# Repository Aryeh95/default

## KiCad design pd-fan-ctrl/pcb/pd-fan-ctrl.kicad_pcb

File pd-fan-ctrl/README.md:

# ESPHome fan controller for a Corsi-Rosenthal box

A small board that runs 12 V PWM PC fans from a USB-C PD charger and puts them in Home Assistant
through ESPHome on a Seeed XIAO ESP32-C6. It is sized for a Corsi-Rosenthal air purifier (140 mm
fans such as the Arctic P14 PWM PST), but works for any 4-pin PWM fans.

- Requests 15 V from any USB-C PD charger of 30 W or more and makes a regulated 12 V fan rail.
- Switches the fan rail fully off, so "off" in Home Assistant stops fans that idle at 0 % PWM.
- 25 kHz PWM, RPM from both fan headers, input voltage, charger protocol and available current.
- I2C and UART headers for an air-quality sensor (3.3 V logic).
- Wi-Fi, Thread or Zigbee firmware builds, a KiCad 9 project, JLCPCB order files and a
  3D-printable case.

The board is rev B: the XIAO plugs into two surface-mount sockets and everything else is
surface-mount, so JLCPCB can assemble it with Economic PCBA. It is 52 × 46 mm, 2-layer. Rev A (a
through-hole version with a 5 V module) was cancelled before it was built; it is in the git
history.

## Layout

```
pcb/         KiCad project, fab/ (Gerbers, BOM, CPL) and docs/ (schematic PDF, renders)
esphome/     firmware: one file per network, plus common/ shared by all three
case/        OpenSCAD case model and STL files
scripts/     generators for the board, schematic and order files
```

**Status: designed and rule-checked, not built.** Measure the 5 V and 12 V rails on the first board
before connecting fans or plugging in the XIAO (see [the first-board checks](#things-to-check-on-the-first-board)). The board passes KiCad DRC with 0 violations and
0 unconnected items, and the schematic, PCB and `design.py` netlists match (33 nets / 142 pins).

A version with an ESP32-C6-MINI-1 module soldered to the board was also designed and then set
aside, because JLCPCB only fits that module with Standard PCBA. Its design and generated files are
in the git history.

## Changes from rev A

- **5 V rail:** a second TPS54302 buck (100 k / 13 k feedback, 5.18 V) replaces the K7805
  through-hole module. Its EN pin is left open, so it is always on.
- **12 V inductor:** TMPA0605S-150MN-D (LCSC C305194; 15 µH, 4 A rated and saturation, 73 mΩ,
  7.3 × 6.6 mm) on JLCPCB's land pattern for it. It is in stock at JLCPCB, so no pre-order is needed.
  The inductor would allow about 7 fans, but the TPS54302 then dissipates
  roughly 0.6–0.7 W in a SOT-23-6, so **treat 5 fans as the limit** until a built board has been
  checked for temperature at full load.
- **5 V inductor:** FXL0518-100-M (10 µH, 2.5 A continuous, 3 A saturation) instead of a 1.95 A part,
  so a short on the 5 V header no longer saturates it before the converter's current limit trips.
- **CH224A on the I2C bus:** its CFG2/SCL and CFG3/SDA pins join the XIAO's I2C bus (the datasheet
  allows 3.3 V logic on them; the board's 4.7 k pull-ups serve both). The CH224A still requests
  15 V by itself through its 56 k resistor. The firmware reads which protocol was negotiated and how
  much current the charger offers ("Charger Max Current" / "Charger Max Power"), so you can see
  whether a charger is big enough for your fans. The CH224A uses I2C address 0x22 or 0x23 (the
  datasheet gives both); don't put a sensor at those addresses on the header.
- **PWM driver base resistor R7** is 1 k (was 2.2 k), so Q3 stays saturated with 7 or more fans
  pulling the PWM line up at once.
- **Extra thermal vias** next to the 12 V converter's ground pin, spreading its heat into the
  bottom copper.
- **FAN2 tach** is read on its own pin (GPIO20) with its own 10 k pull-up and 10 k series resistor.
  FAN1's series resistor is also 10 k now, which protects the GPIO from fans that pull tach up to 12 V.
- **USB-C socket:** 16-pin TYPE-C-31-M-12 (its data pins are unused).
- **PD_PG pull-up** removed; the firmware uses the ESP32's internal pull-up.
- **Fan-header peg holes** are 1.3 mm (Molex recommends 1.25 mm; the KiCad library has 1.1 mm) so
  machine-inserted headers seat flat.
- **VBUS test pad (TP1)** next to the 12 V converter, for measuring the charger voltage.
- **Wider supply tracks:** the charger input (VBUS) is 0.8 mm wide (was 0.5 mm) for 7-fan loads, and
  no longer passes through a resistor pad on the way to the 5 V converter. The 12 V fan rail is 1 mm.
- **CH224A ground pad** has two vias straight down to the bottom ground plane (its exposed pad is
  its only ground pin).
- **CH224A DP/DM** are shorted together at the chip and not connected to the USB-C socket, as the
  datasheet describes for PD-only use. This turns off the QC/BC 1.2 fallbacks, which could only
  offer 5–12 V anyway; the fans need the 15 V PD profile.
- **Ground plane:** signal tracks on the bottom layer cut from about 260 mm to 150 mm. Estimated ground
  resistance from the USB-C socket and the 12 V output capacitors to the 12 V converter is now
  0.5–0.7 mΩ (a solid plane would be about 0.4 mΩ).

### Things to check on the first board

- **CH224A VBUS pin (R16):** the datasheet's reference circuit ties it straight to VBUS (as here,
  through R16 = 0 Ω), while its pin table says the pin tolerates 3.8 V. If PD negotiation misbehaves
  or U1 runs hot, this is the first thing to look at.
- **12 V converter temperature** with all fans at 100 %.
- **CH224A I2C:** check the boot log's I2C scan finds it at 0x22 or 0x23, and that "Charger Max
  Current" matches the charger's label. If the CH224A misbehaves with the bus connected, the
  sensors can be removed from the firmware, since it requests 15 V from its resistor with no I2C
  traffic needed.
- **Wi-Fi signal** with the XIAO in its sockets, compared with a bare XIAO (the 5 V converter is
  about 6 mm from the antenna end, 7.5 mm below it).
- Pull the XIAO **straight up** out of the SMD sockets; they're held only by their solder pads.

## Ordering

1. Upload `pcb/fab/*-gerbers.zip`. 2 layers, 1.6 mm, any solder-mask colour (green and blue were
   both quoted with Economic PCBA; colours other than green add about 2 days to the build time),
   HASL with or without lead. Don't pick OSP: that finish forces
   Standard PCBA.
2. PCB Assembly, **Economic**, top side. Upload a BOM and the CPL with the same suffix:
   - `*-jlcpcb.csv`: surface-mount parts only; you solder the fan headers.
   - `*-fanhdr-C19795120.csv`: JLCPCB also fits the fan headers (Molex 470533000). This was quoted
     as Economic PCBA with a small handling fee per header.
3. In the placement preview, check the orientation of U1, U4, U5, Q3, D1, J1, J6, J7 and the fan
   headers (locking ramp along the bottom board edge). L1 and L2 haven't been seen in JLCPCB's
   viewer yet; both are two-pad parts, so only their position matters.

### Seeed Fusion PCBA

The same board can be assembled by Seeed Fusion instead. Seeed buys parts by manufacturer part
number, so it has its own files in `pcb/fab/`:

- `*-gerbers.zip`, the same Gerbers as for JLCPCB.
- `*-bom-seeed.csv` and `*-cpl-seeed.csv`: surface-mount parts only; you solder the fan headers.
- `*-bom-seeed-fanhdr.csv` and `*-cpl-seeed-fanhdr.csv`: Seeed also fits the fan headers
  (Molex 47053-1000, through-hole).
- `*-assembly-top.pdf`: outlines, reference designators and pin-1 marks, for Seeed's
  orientation check.

The BOM has Designator, Manufacturer Part Number, Quantity and an LCSC link for each part, as in
Seeed's template. The placement file uses KiCad's own rotations (the JLCPCB files carry JLCPCB's
corrections). Several parts come from Chinese makers that Seeed may not stock (CH224A, the SMD
sockets, both inductors); the links help their buyers, and Seeed may propose equivalents.

## XIAO notes

- Pin use is the same as rev A, plus D9 (GPIO20) for FAN2 tach.
- Buy bare XIAOs and solder short (about 7.5 mm) 1×7 male headers to them, with the XIAO plugged
  into the board so the pins line up. The SMD sockets have closed bottoms, so long standard headers
  may not seat.
- The sockets are 5 mm tall; the case model assumes that.

## Firmware

There are three builds of the same firmware. Pick one and flash it over the XIAO's own USB
port the first time.

| File | Network | Home Assistant sees | Updates |
|---|---|---|---|
| `pd-fan-ctrl-wifi.yaml` | Wi-Fi, with a fallback hotspot | Fan entity with speed, all sensors | Over Wi-Fi |
| `pd-fan-ctrl-thread.yaml` | Thread (needs a border router) | Same as Wi-Fi | Over Thread |
| `pd-fan-ctrl-zigbee.yaml` | Zigbee router (ZHA or Zigbee2MQTT) | "Fan Power" switch and "Fan Speed" number, the sensors, no "Charger Protocol" | USB only |

- ESPHome can't run Wi-Fi and Thread at the same time, or Zigbee and Thread, so each build
  has one network. To change network, flash a different build: Wi-Fi to Thread works over the
  air; going to Zigbee, or back from Zigbee, needs the USB cable.
- **Thread** needs your network's dataset in `secrets.yaml` as `thread_tlv` (Home Assistant:
  Settings > Devices & services > Thread > Configure > the (i) on your network > Active dataset
  TLVs).
- **Zigbee** support in ESPHome is new and only exposes switches, numbers, sensors and binary
  sensors, so the fan is a switch plus a 0–100 % number and "Reset Filter Hours" is a switch
  that turns itself off. Zigbee2MQTT may show the device as generic endpoints.
- All three were compiled with ESPHome 2026.10.2 but none has run on hardware yet.

### Other XIAO boards

The board takes any XIAO ESP32 with the standard 14-pin layout. Pick yours in the `board:`
line near the top of the firmware file; the board files in `esphome/boards/` hold each chip's
settings and pin numbers.

| Board file | XIAO | Networks | Antenna |
|---|---|---|---|
| `xiao-esp32c6.yaml` (default) | ESP32-C6 | Wi-Fi, Thread, Zigbee | On the board |
| `xiao-esp32c5.yaml` | ESP32-C5 | Wi-Fi (2.4 and 5 GHz), Thread, Zigbee | External, U.FL |
| `xiao-esp32c3.yaml` | ESP32-C3 | Wi-Fi | External, U.FL |
| `xiao-esp32s3.yaml` | ESP32-S3 | Wi-Fi | External, U.FL |
| `xiao-esp32s3-plus.yaml` | ESP32-S3 Plus | Wi-Fi | External, U.FL |

- Boards with an external antenna come with a flexible one; stick it inside the case lid.
- ESPHome warns about "strapping pins" when compiling for the C3, C5 and S3. The board holds
  those pins at safe levels at power-on (see the notes in each board file), so the warnings are
  expected. On the C3, D0 is also pulled low by the voltage divider when no charger is
  connected; this only matters for the boot-button flashing mode, so check USB flashing on the
  first C3.
- The board was designed around the C6. The other boards' pins were checked against Seeed's pin
  maps and their firmware compiles, but none has been tried on the board.

## Files

| Path | What it is |
|---|---|
| `pcb/pd-fan-ctrl.kicad_pro`, `.kicad_sch`, `.kicad_pcb` | KiCad 9 project |
| `pcb/docs/` | Schematic PDF, 3D render, assembly drawing (with reference designators), case preview |
| `pcb/fab/` | Gerbers, JLCPCB BOM and CPL files, hand-solder list |
| `esphome/pd-fan-ctrl-wifi.yaml`, `-thread.yaml`, `-zigbee.yaml` | Firmware, one per network (see [Firmware](#firmware)) |
| `esphome/common/pd-fan-ctrl-core.yaml` | Fan control and sensors shared by all three |
| `esphome/boards/` | Chip settings and pin numbers for each XIAO |
| `case/` | OpenSCAD case model and STL files |
| `scripts/` | Generators |

## Regenerating

```sh
cd scripts
python3 gen_board.py place     # footprints, outline, zones
python3 route.py               # tracks, vias, silkscreen, pour, stitching
python3 drc.py                 # KiCad DRC summary
python3 gen_sch.py             # schematic
python3 check_netlist.py       # schematic == PCB == design.py
python3 gen_fab.py             # Gerbers, BOM, CPL, schematic PDF
```

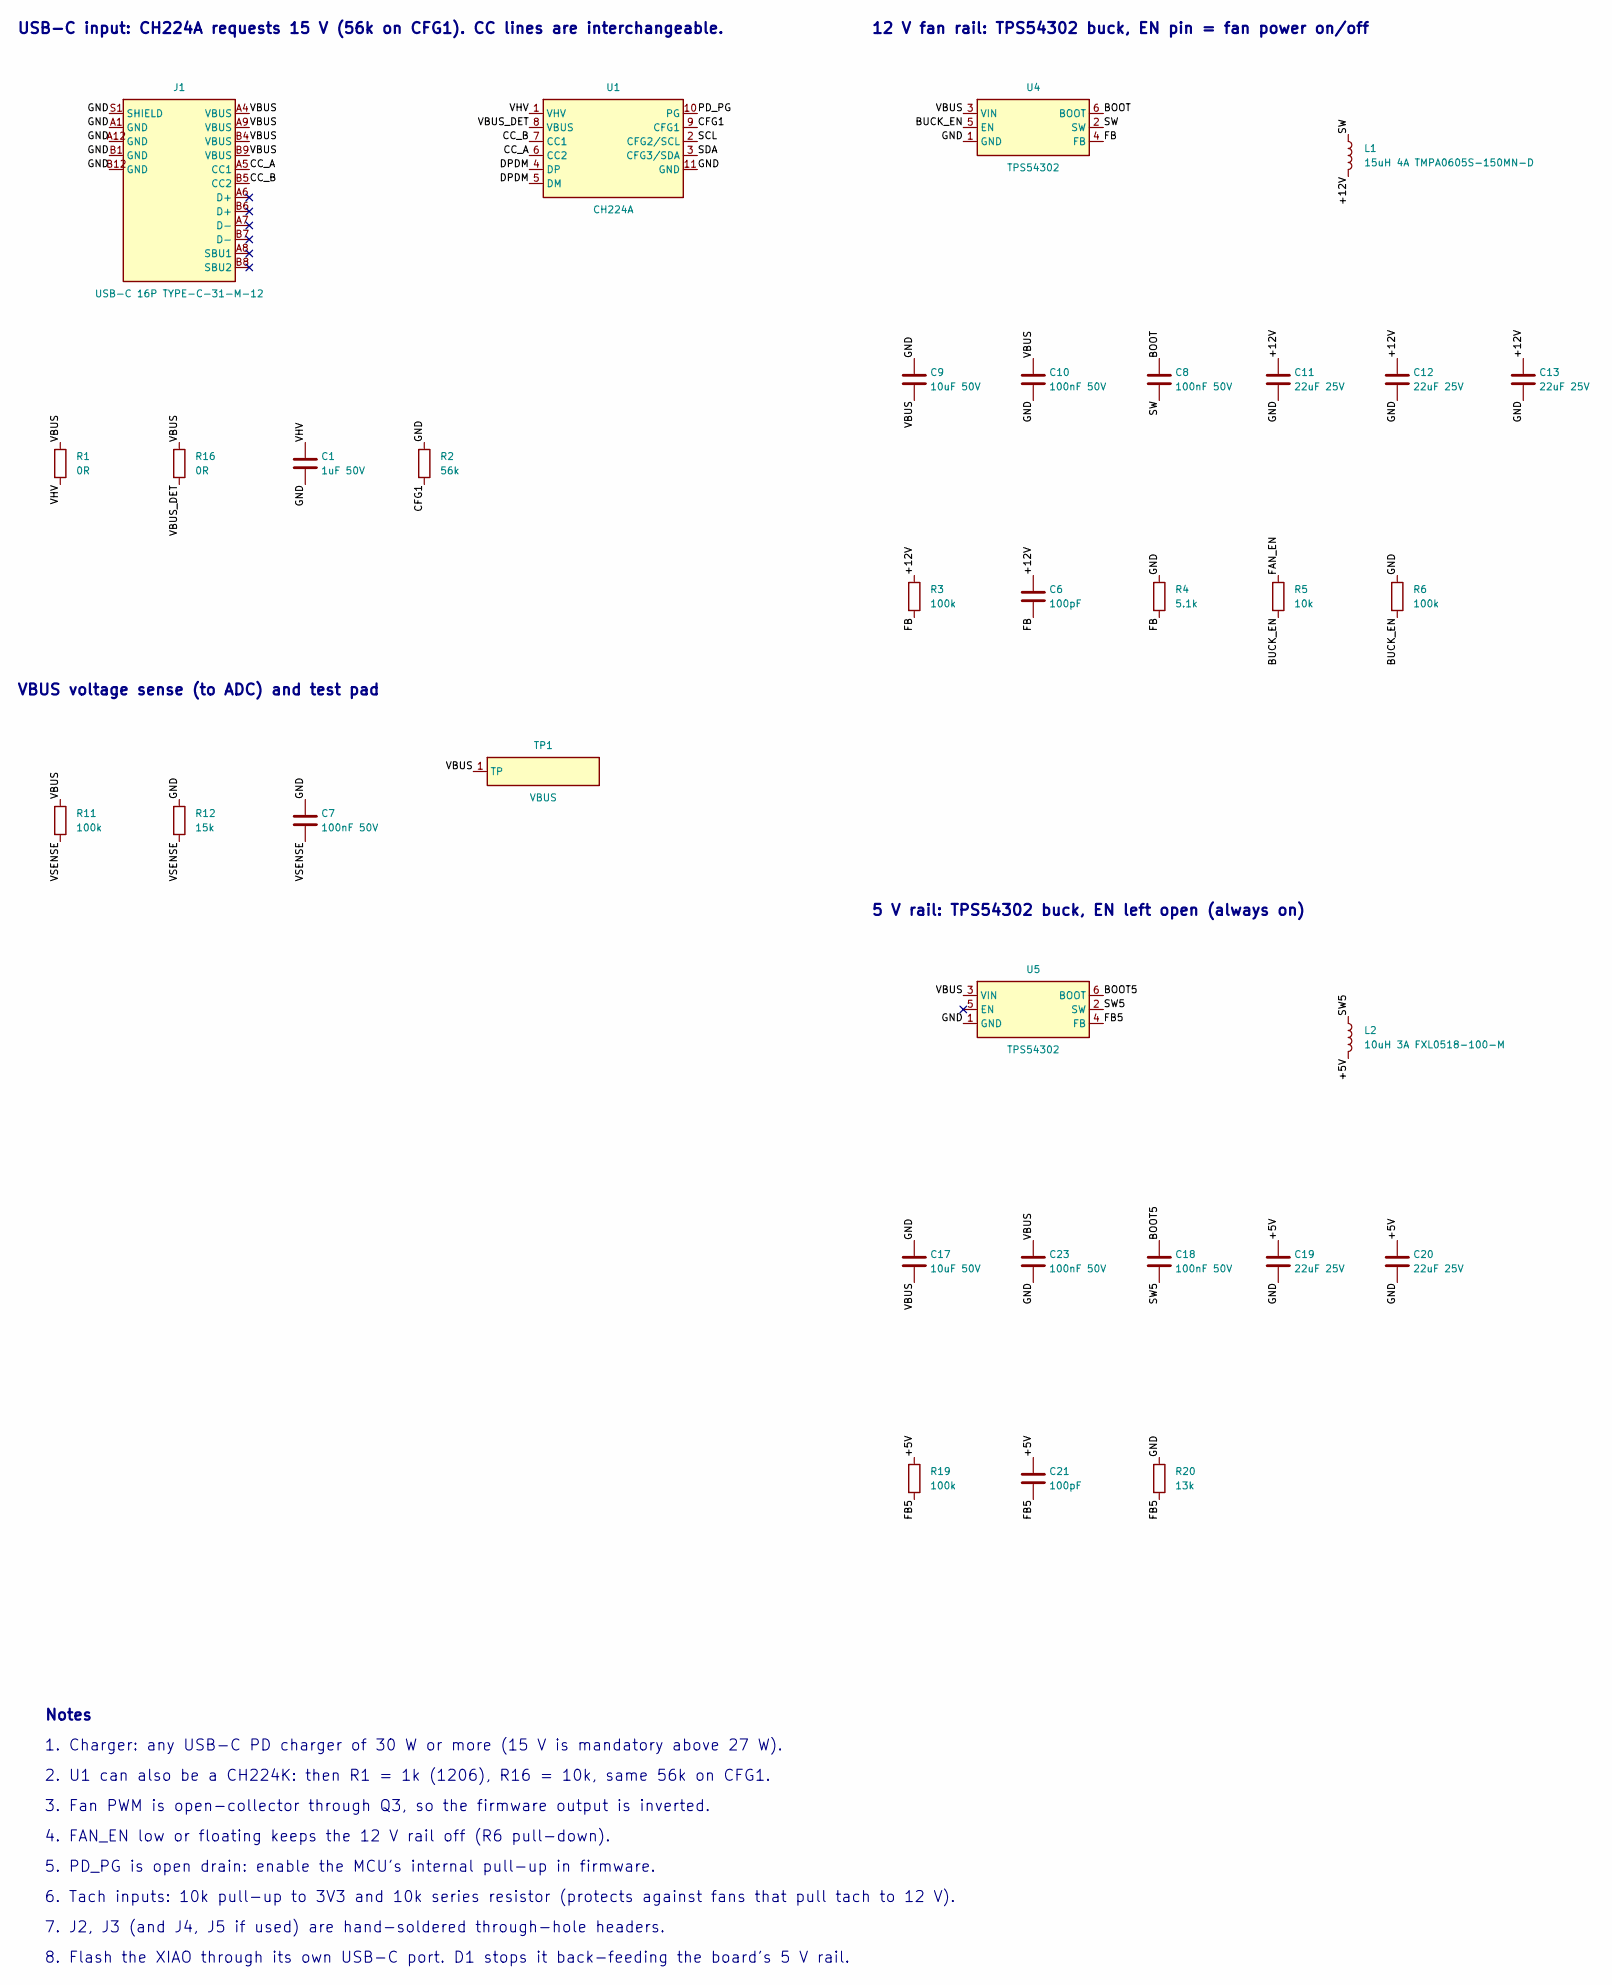
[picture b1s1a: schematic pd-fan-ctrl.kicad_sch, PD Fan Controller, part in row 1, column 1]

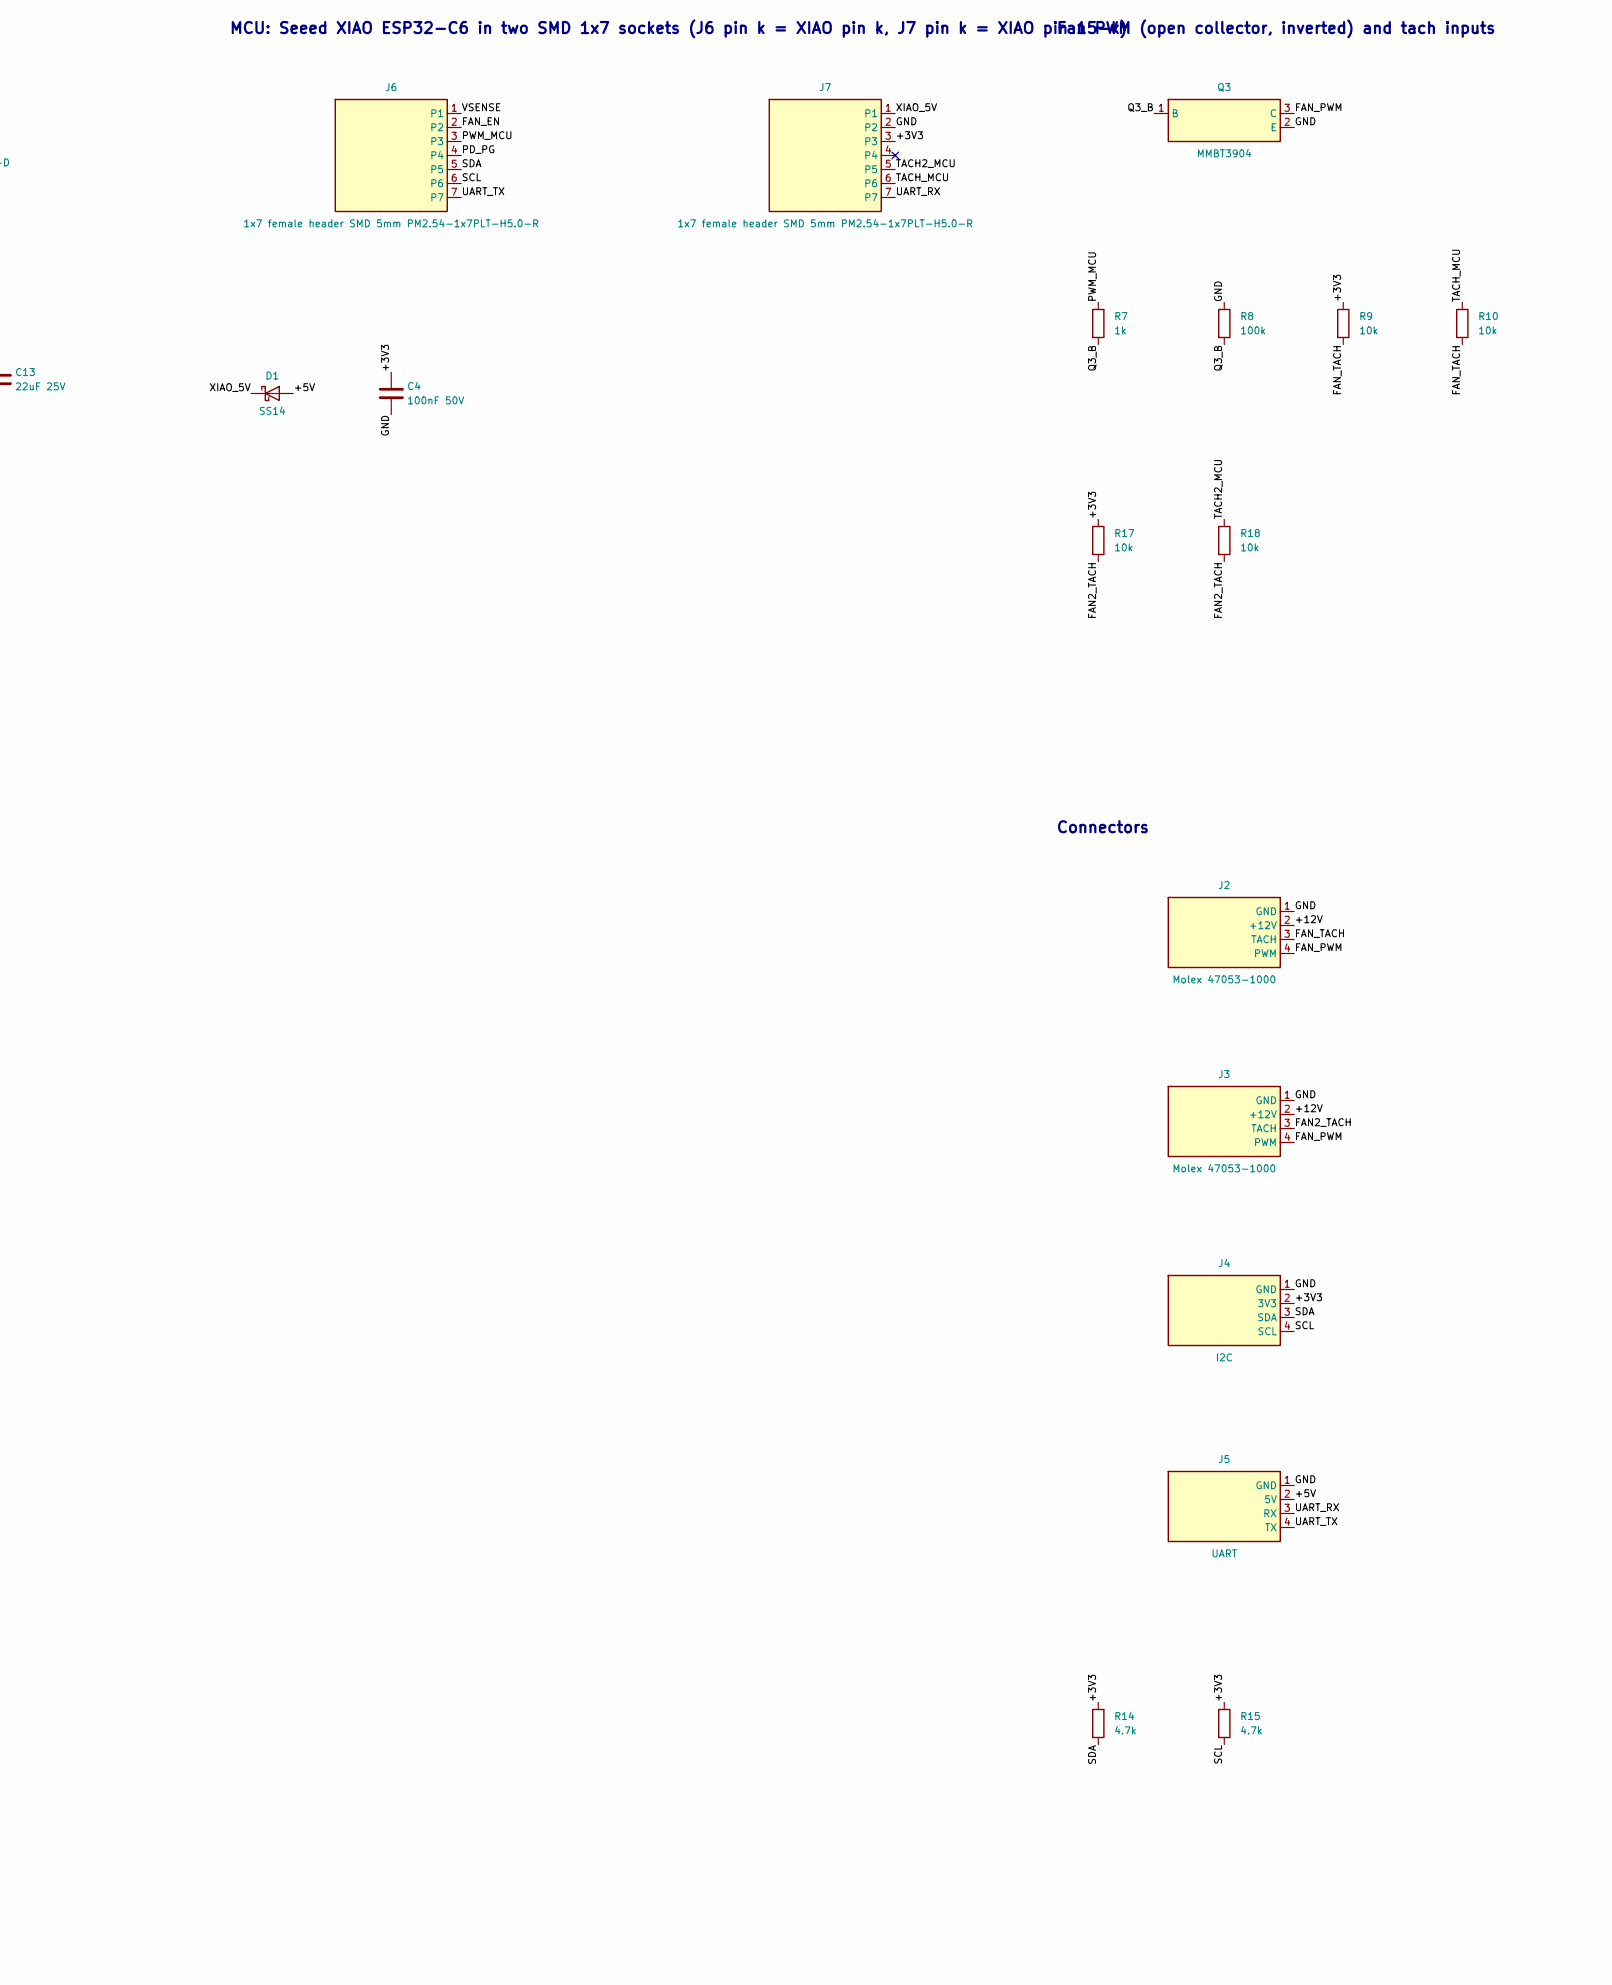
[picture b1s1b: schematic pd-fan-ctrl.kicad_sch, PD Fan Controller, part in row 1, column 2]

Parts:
C1: 1uF 50V; C_0603_1608Metric; LCSC C15849
C4, C7, C8, C10, C18, C23: 100nF 50V; C_0603_1608Metric; LCSC C14663
C6, C21: 100pF; C_0603_1608Metric; LCSC C14858
C9, C17: 10uF 50V; C_1206_3216Metric; LCSC C13585
C11, C12, C13, C19, C20: 22uF 25V; C_1206_3216Metric; LCSC C12891
D1: SS14; D_SMA; LCSC C2480
J1: USB-C 16P TYPE-C-31-M-12; USB_C_Receptacle_HRO_TYPE-C-31-M-12; LCSC C165948
J2, J3: Molex 47053-1000; FanPinHeader_1x04_P2.54mm_Vertical; LCSC C240840
J4: I2C; PinHeader_1x04_P2.54mm_Vertical
J5: UART; PinHeader_1x04_P2.54mm_Vertical
J6, J7: 1x7 female header SMD 5mm PM2.54-1x7PLT-H5.0-R; SOCKET_1x7_SMD; LCSC C55218891
L1: 15uH 4A TMPA0605S-150MN-D; L_TMPA0605S; LCSC C305194
L2: 10uH 3A FXL0518-100-M; L_Changjiang_FXL0518; LCSC C475910
Q3: MMBT3904; SOT-23; LCSC C20526
R1: 0R; R_1206_3216Metric; LCSC C17888
R2: 56k; R_0603_1608Metric; LCSC C23206
R3, R6, R8, R11, R19: 100k; R_0603_1608Metric; LCSC C25803
R4: 5.1k; R_0603_1608Metric; LCSC C23186
R5, R9, R10, R17, R18: 10k; R_0603_1608Metric; LCSC C25804
R7: 1k; R_0603_1608Metric; LCSC C21190
R12: 15k; R_0603_1608Metric; LCSC C22809
R14, R15: 4.7k; R_0603_1608Metric; LCSC C23162
R16: 0R; R_0603_1608Metric; LCSC C21189
R20: 13k; R_0603_1608Metric; LCSC C22797
TP1: VBUS; TestPoint_Pad_D1.5mm
U1: CH224A; SSOP-10-1EP_3.9x4.9mm_P1mm_EP2.1x3.3mm; LCSC C42459160
U4, U5: TPS54302; TSOT-23-6; LCSC C311983

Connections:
+3V3: C4.1, J4.2 (3V3), J7.3, R9.1, R14.1, R15.1, R17.1
+5V: C19.1, C20.1, C21.1, D1.2 (A), J5.2 (5V), L2.2, R19.1
+12V: C6.1, C11.1, C12.1, C13.1, J2.2 (+12V), J3.2 (+12V), L1.2, R3.1
BOOT: C8.1, U4.6 (BOOT)
BOOT5: C18.1, U5.6 (BOOT)
BUCK_EN: R5.2, R6.2, U4.5 (EN)
CC_A: J1.A5 (CC1), U1.6 (CC2)
CC_B: J1.B5 (CC2), U1.7 (CC1)
CFG1: R2.2, U1.9 (CFG1)
DPDM: U1.4 (DP), U1.5 (DM)
FAN2_TACH: J3.3 (TACH), R17.2, R18.2
FAN_EN: J6.2, R5.1
FAN_PWM: J2.4 (PWM), J3.4 (PWM), Q3.3 (C)
FAN_TACH: J2.3 (TACH), R9.2, R10.2
FB: C6.2, R3.2, R4.2, U4.4 (FB)
FB5: C21.2, R19.2, R20.2, U5.4 (FB)
GND: C1.2, C4.2, C7.1, C9.1, C10.2, C11.2, C12.2, C13.2, C17.1, C19.2, C20.2, C23.2, J1.A1 (GND), J1.A12 (GND), J1.B1 (GND), J1.B12 (GND), J1.S1 (SHIELD), J2.1 (GND), J3.1 (GND), J4.1 (GND), J5.1 (GND), J7.2, Q3.2 (E), R2.1, R4.1, R6.1, R8.1, R12.1, R20.1, U1.11 (GND), U4.1 (GND), U5.1 (GND)
PD_PG: J6.4, U1.10 (PG)
PWM_MCU: J6.3, R7.1
Q3_B: Q3.1 (B), R7.2, R8.2
SCL: J4.4 (SCL), J6.6, R15.2, U1.2 (CFG2/SCL)
SDA: J4.3 (SDA), J6.5, R14.2, U1.3 (CFG3/SDA)
SW: C8.2, L1.1, U4.2 (SW)
SW5: C18.2, L2.1, U5.2 (SW)
TACH2_MCU: J7.5, R18.1
TACH_MCU: J7.6, R10.1
UART_RX: J5.3 (RX), J7.7
UART_TX: J5.4 (TX), J6.7
VBUS: C9.2, C10.1, C17.2, C23.1, J1.A4 (VBUS), J1.A9 (VBUS), J1.B4 (VBUS), J1.B9 (VBUS), R1.1, R11.1, R16.1, TP1.1, U4.3 (VIN), U5.3 (VIN)
VBUS_DET: R16.2, U1.8 (VBUS)
VHV: C1.1, R1.2, U1.1 (VHV)
VSENSE: C7.2, J6.1, R11.2, R12.2
XIAO_5V: D1.1 (K), J7.1

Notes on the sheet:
USB-C input: CH224A requests 15 V (56k on CFG1). CC lines are interchangeable.
VBUS voltage sense (to ADC) and test pad
12 V fan rail: TPS54302 buck, EN pin = fan power on/off
5 V rail: TPS54302 buck, EN left open (always on)
Fan PWM (open collector, inverted) and tach inputs
Connectors
MCU: Seeed XIAO ESP32-C6 in two SMD 1x7 sockets (J6 pin k = XIAO pin k, J7 pin k = XIAO pin 15-k)
Notes
1. Charger: any USB-C PD charger of 30 W or more (15 V is mandatory above 27 W).
2. U1 can also be a CH224K: then R1 = 1k (1206), R16 = 10k, same 56k on CFG1.
3. Fan PWM is open-collector through Q3, so the firmware output is inverted.
4. FAN_EN low or floating keeps the 12 V rail off (R6 pull-down).
5. PD_PG is open drain: enable the MCU's internal pull-up in firmware.
6. Tach inputs: 10k pull-up to 3V3 and 10k series resistor (protects against fans that pull tach to 12 V).
7. J2, J3 (and J4, J5 if used) are hand-soldered through-hole headers.
8. Flash the XIAO through its own USB-C port. D1 stops it back-feeding the board's 5 V rail.

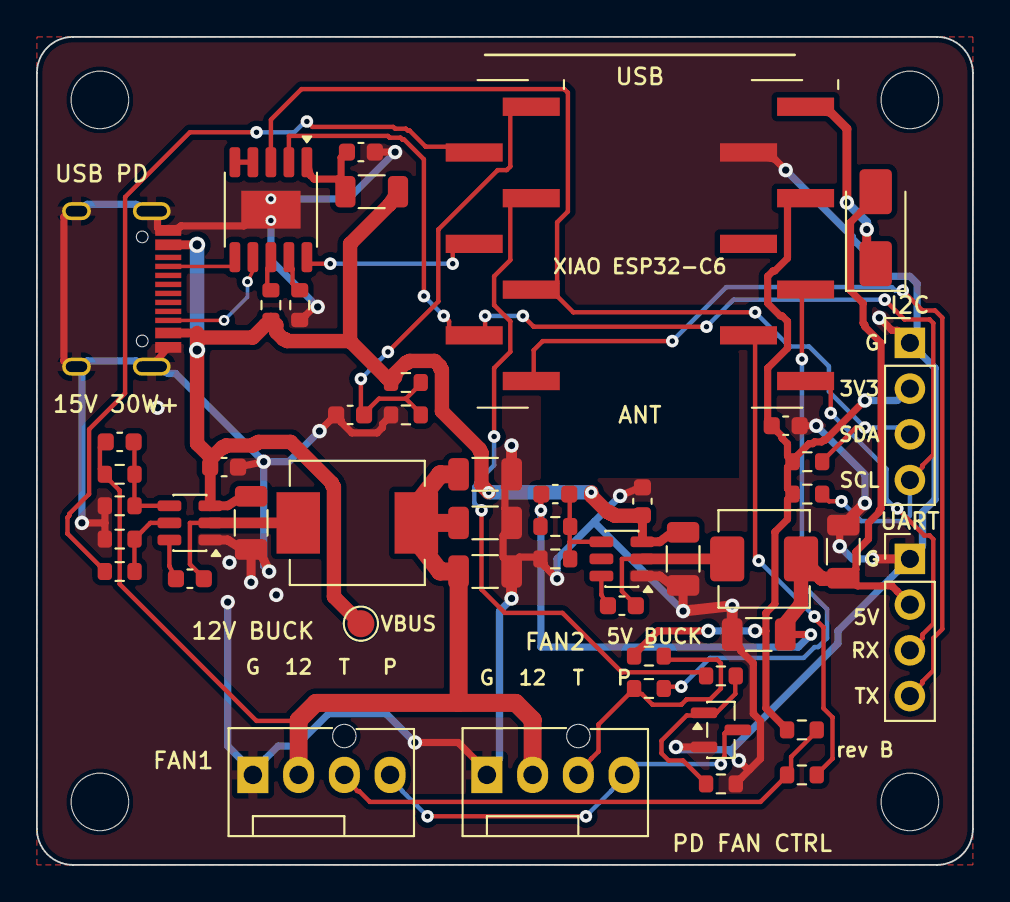
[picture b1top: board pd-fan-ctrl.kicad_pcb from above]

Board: 2 copper layers, 52.0 x 46.0 mm, 54 parts (0 on the bottom side), 33 nets.

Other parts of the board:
H1, H2, H3, H4: MountingHole_3.2mm_M3

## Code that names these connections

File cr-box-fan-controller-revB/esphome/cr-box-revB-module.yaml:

# ESPHome config for the CR Box fan controller, rev B with an ESP32-C6-MINI-1 module
#
# Pin map (module pin -> GPIO -> board net)
#   9   GPIO4   VSENSE    USB-C input voltage (100k / 15k divider, ADC1_CH4)
#   12  GPIO0   FAN_EN    high = 12 V fan rail on
#   27  GPIO21  PWM_MCU   25 kHz fan PWM, inverted (open-collector driver)
#   10  GPIO5   PD_PG     low = USB PD negotiation succeeded (open drain, internal pull-up)
#   28  GPIO22  SDA       I2C header
#   29  GPIO23  SCL       I2C header
#   31  GPIO16  TX        UART header (TXD0)
#   30  GPIO17  RX        UART header (RXD0)
#   25  GPIO19  TACH_MCU  FAN1 tach, 2 pulses per revolution
#   26  GPIO20  TACH2_MCU FAN2 tach, 2 pulses per revolution
#   17/18 GPIO12/13       USB D-/D+ on the board's USB-C port (flashing and logs)
#   23  GPIO9   BOOT button (hold while pressing RESET to force download mode)
#
# First flash: plug the board into a computer with a USB-C data cable and flash
# over USB (esphome run ...). The fans stay off on a computer's 5 V; that's expected.

esphome:
  name: cr-box
  friendly_name: CR Box

esp32:
  board: esp32-c6-devkitc-1
  variant: esp32c6
  flash_size: 4MB
  framework:
    type: esp-idf

logger:
  hardware_uart: USB_SERIAL_JTAG
api:
ota:
  - platform: esphome

wifi:
  ssid: !secret wifi_ssid
  password: !secret wifi_password
  ap: {}

captive_portal:

output:
  - platform: ledc
    id: fan_pwm
    pin: GPIO21
    frequency: 25000 Hz
    inverted: true          # Q3 pulls the fan PWM line low when the pin is high

switch:
  - platform: gpio
    id: fan_power           # 12 V fan rail (TPS54302 enable)
    pin: GPIO0
    restore_mode: ALWAYS_OFF
    internal: true

globals:
  - id: duty                # PWM level currently applied to the fans, 0..1
    type: float
    initial_value: '0'

fan:
  - platform: template
    id: purifier
    name: "Purifier Fan"
    speed_count: 100
    restore_mode: RESTORE_DEFAULT_ON
    on_state:
      - script.execute: apply_fan

script:
  # Applies the fan entity's state to the hardware.
  # - The 12 V rail is only switched on while the charger supplies 15 V
  #   ("Charger OK"); on a 5 V-only supply the fans stay off.
  # - On start-up the fans begin at 20 % and ramp to the set speed in 5 % steps
  #   every 100 ms, so 4-5 fans don't all draw full start-up current at once.
  - id: apply_fan
    mode: restart
    then:
      - if:
          condition:
            lambda: 'return id(purifier).state && id(charger_ok).state;'
          then:
            - if:
                condition:
                  switch.is_off: fan_power
                then:
                  - lambda: |-
                      id(duty) = 0.2f;
                      id(fan_pwm).set_level(id(duty));
                  - switch.turn_on: fan_power
                  - delay: 500ms
            - while:
                condition:
                  lambda: 'return fabsf(id(duty) - id(purifier).speed / 100.0f) > 0.001f;'
                then:
                  - lambda: |-
                      const float target = id(purifier).speed / 100.0f;
                      const float step = 0.05f;
                      if (id(duty) < target) id(duty) = std::min(target, id(duty) + step);
                      else id(duty) = std::max(target, id(duty) - step);
                      id(fan_pwm).set_level(id(duty));
                  - delay: 100ms
          else:
            - switch.turn_off: fan_power
            - lambda: |-
                id(duty) = 0.0f;
                id(fan_pwm).set_level(0.0f);

sensor:
  - platform: pulse_counter
    name: "Fan 1 RPM"
    pin: GPIO19
    unit_of_measurement: "RPM"
    accuracy_decimals: 0
    update_interval: 10s
    filters:
      - multiply: 0.5       # 2 pulses per revolution

  - platform: pulse_counter
    name: "Fan 2 RPM"
    pin: GPIO20
    unit_of_measurement: "RPM"
    accuracy_decimals: 0
    update_interval: 10s
    filters:
      - multiply: 0.5       # 2 pulses per revolution

  - platform: adc
    name: "Input Voltage"
    id: vbus
    pin:
      number: GPIO4
      # strapping pin, but only for the SDIO sampling edge, which this board doesn't use
      ignore_strapping_warning: true
    attenuation: 12db
    update_interval: 2s
    accuracy_decimals: 1
    filters:
      - multiply: 7.667     # (100k + 15k) / 15k
      - sliding_window_moving_average:
          window_size: 3
          send_every: 1

binary_sensor:
  - platform: gpio
    name: "USB PD Negotiated"
    pin:
      number: GPIO5
      ignore_strapping_warning: true   # MTDI strap only selects the SDIO edge
      inverted: true
      mode:
        input: true
        pullup: true        # rev B has no external pull-up on PD_PG
    entity_category: diagnostic

  # Gates the 12 V fan rail: true while the charger supplies 15 V.
  - platform: template
    id: charger_ok
    name: "Charger OK"
    device_class: power
    entity_category: diagnostic
    lambda: 'return id(vbus).has_state() && id(vbus).state > 13.5;'
    filters:
      - delayed_off: 2s     # ignore a brief dip when the fans start
    on_state:
      - script.execute: apply_fan

# Optional sensors on the headers. Both headers use 3.3 V logic. The UART header
# supplies 5 V power, which suits sensors like the PMS5003 or SEN55 (5 V power,
# 3.3 V logic). A sensor with 5 V logic needs a voltage divider on its TX line.
# For example:
# i2c:
#   sda: GPIO22
#   scl: GPIO23
# uart:
#   tx_pin: GPIO16
#   rx_pin: GPIO17
#   baud_rate: 9600
